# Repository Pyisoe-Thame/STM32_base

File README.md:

# Relay with AC PS and STM32

This is my PCB Design practice project.
Flexible programming expandable with sensors through I2C.

## Screenshots

<p align="center">PCB Design</p>

<p align="center">3D View</p>

## Features

- AC Power Supply to 5V, 3V3
- STM32F103C8T6
- SWD J Tag Connector
- USB Type C 2.0
- USART, I2C
- 5V Relay

## License

[MIT](https://choosealicense.com/licenses/mit/)

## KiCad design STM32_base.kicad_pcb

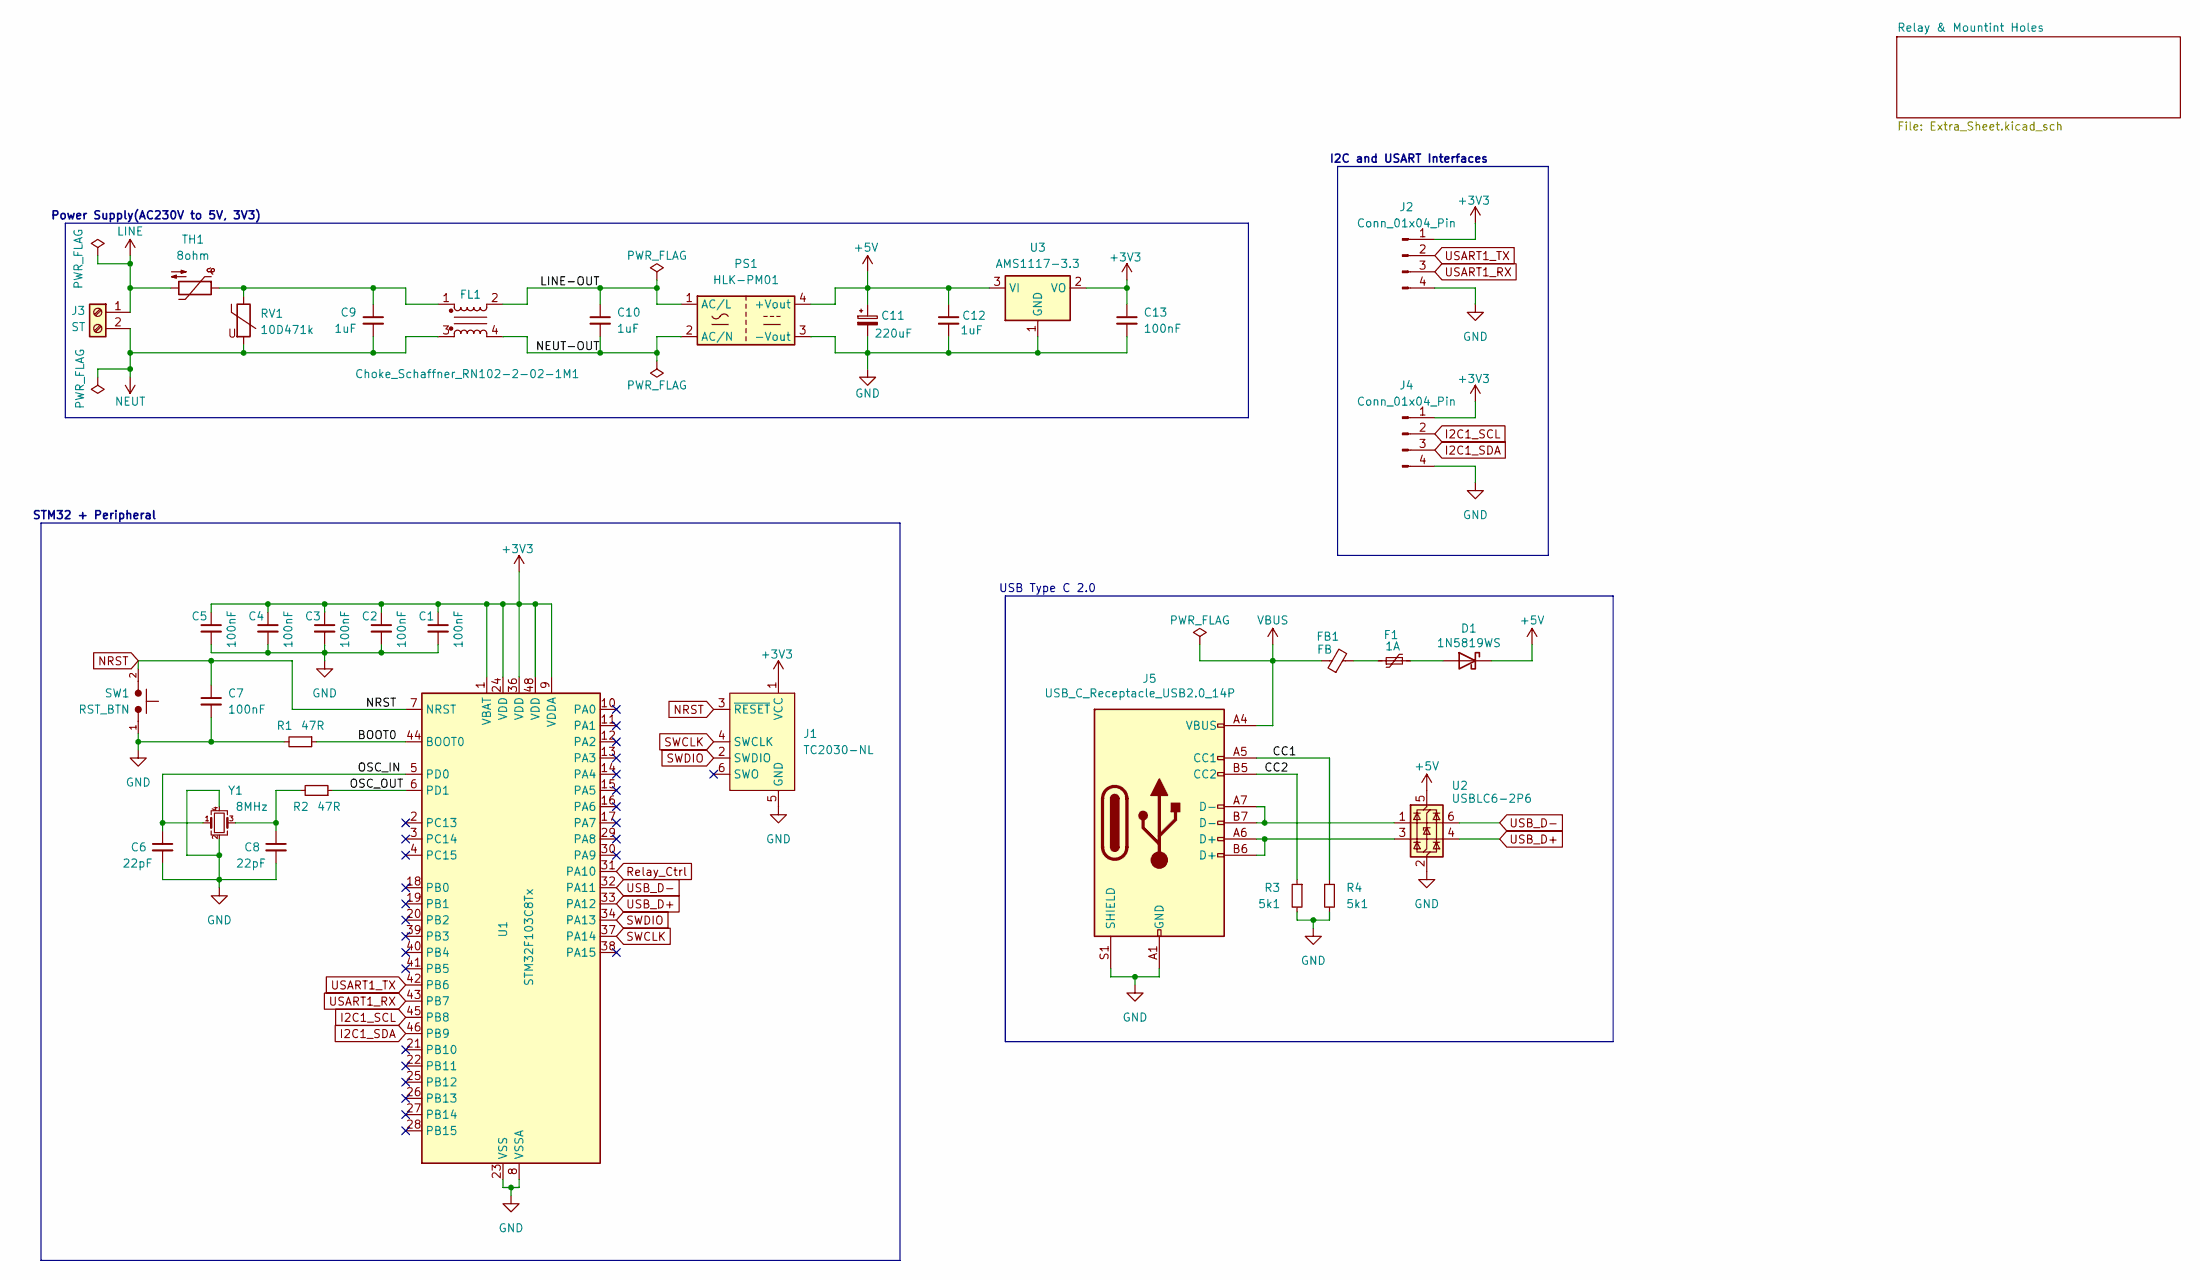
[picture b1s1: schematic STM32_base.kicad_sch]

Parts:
C1, C2, C3, C4, C5, C7, C13: 100nF; C_0402_1005Metric
C6, C8: 22pF; C_0402_1005Metric
C9, C10: 1uF; C_Rect_L18.0mm_W9.0mm_P15.00mm_FKS3_FKP3
C11: 220uF; CP_Elec_10x10
C12: 1uF; C_0603_1608Metric
D1: 1N5819WS; D_SOD-323
F1: 1A; Fuse_1206_3216Metric
FB1: FB; L_0603_1608Metric
FL1: Choke_Schaffner_RN102-2-02-1M1; Choke_Schaffner_RN102-04-14.0x14.0mm
J1: TC2030-NL; Tag-Connect_TC2030-IDC-NL_2x03_P1.27mm_Vertical
J2, J4: Conn_01x04_Pin; PinHeader_1x04_P2.54mm_Vertical
J3: ST; TerminalBlock_Phoenix_MKDS-1,5-2-5.08_1x02_P5.08mm_Horizont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
J5: USB_C_Receptacle_USB2.0_14P; USB_C_Receptacle_HRO_TYPE-C-31-M-12
PS1: HLK-PM01; Converter_ACDC_Hi-Link_HLK-PMxx
R1, R2: 47R; R_0603_1608Metric
R3, R4: 5k1; R_0603_1608Metric
RV1: 10D471k; RV_Disc_D12mm_W4.7mm_P7.5mm
SW1: RST_BTN; SW_PUSH_6mm
TH1: 8ohm; RV_Disc_D12mm_W4.7mm_P7.5mm
U1: STM32F103C8Tx; LQFP-48_7x7mm_P0.5mm
U2: USBLC6-2P6; SOT-666
U3: AMS1117-3.3; SOT-223-3_TabPin2
Y1: 8MHz; Crystal_SMD_3225-4Pin_3.2x2.5mm

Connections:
+3V3: C1.1, C2.1, C3.1, C4.1, C5.1, C13.1, J1.1 (VCC), J2.1, J4.1, U1.1 (VBAT), U1.9 (VDDA), U1.24 (VDD), U1.36 (VDD), U1.48 (VDD), U3.2 (VO)
+5V: C11.1, C12.1, D1.1 (K), PS1.4 (+Vout), U2.5 (VBUS), U3.3 (VI); also elsewhere on the board
/BOOT0: R1.1, U1.44 (BOOT0)
/CC1: J5.A5 (CC1), R4.1
/CC2: J5.B5 (CC2), R3.1
/LINE-OUT: C10.1, FL1.2, PS1.1 (AC/L)
/NEUT-OUT: C10.2, FL1.4, PS1.2 (AC/N)
/OSC_IN: C6.1, U1.5 (PD0), Y1.1
/OSC_OUT: R2.1, U1.6 (PD1)
GND: C1.2, C2.2, C3.2, C4.2, C5.2, C6.2, C7.2, C8.2, C11.2, C12.2, C13.2, J1.5 (GND), J2.4, J4.4, J5.A1 (GND), J5.A12 (GND), J5.B1 (GND), J5.B12 (GND), J5.S1 (SHIELD), PS1.3 (-Vout), R1.2, R3.2, R4.2, SW1.1, U1.8 (VSSA), U1.23 (VSS), U1.35 (VSS), U1.47 (VSS), U2.2 (GND), U3.1 (GND), Y1.2, Y1.4; also elsewhere on the board
I2C1_SCL: J4.2, U1.45 (PB8)
I2C1_SDA: J4.3, U1.46 (PB9)
LINE: J3.1, TH1.2
NEUT: C9.2, FL1.3, J3.2, RV1.2
NRST: C7.1, J1.3 (~RESET), SW1.2, U1.7 (NRST)
unnamed: C8.1, R2.2, Y1.3
unnamed: C9.1, FL1.1, RV1.1, TH1.1
unnamed: D1.2 (A), F1.2
unnamed: F1.1, FB1.2
unnamed: J5.A6 (D+), J5.B6 (D+), U2.3 (I/O2)
unnamed: J5.A7 (D-), J5.B7 (D-), U2.1 (I/O1)
Relay_Ctrl: U1.31 (PA10); also elsewhere on the board
SWCLK: J1.4 (SWCLK), U1.37 (PA14)
SWDIO: J1.2 (SWDIO), U1.34 (PA13)
USART1_RX: J2.3, U1.43 (PB7)
USART1_TX: J2.2, U1.42 (PB6)
USB_D+: U1.33 (PA12), U2.4 (I/O2)
USB_D-: U1.32 (PA11), U2.6 (I/O1)
VBUS: FB1.1, J5.A4 (VBUS), J5.A9 (VBUS), J5.B4 (VBUS), J5.B9 (VBUS)

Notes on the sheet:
I2C and USART Interfaces
STM32 + Peripheral
Power Supply(AC230V to 5V, 3V3)
USB Type C 2.0

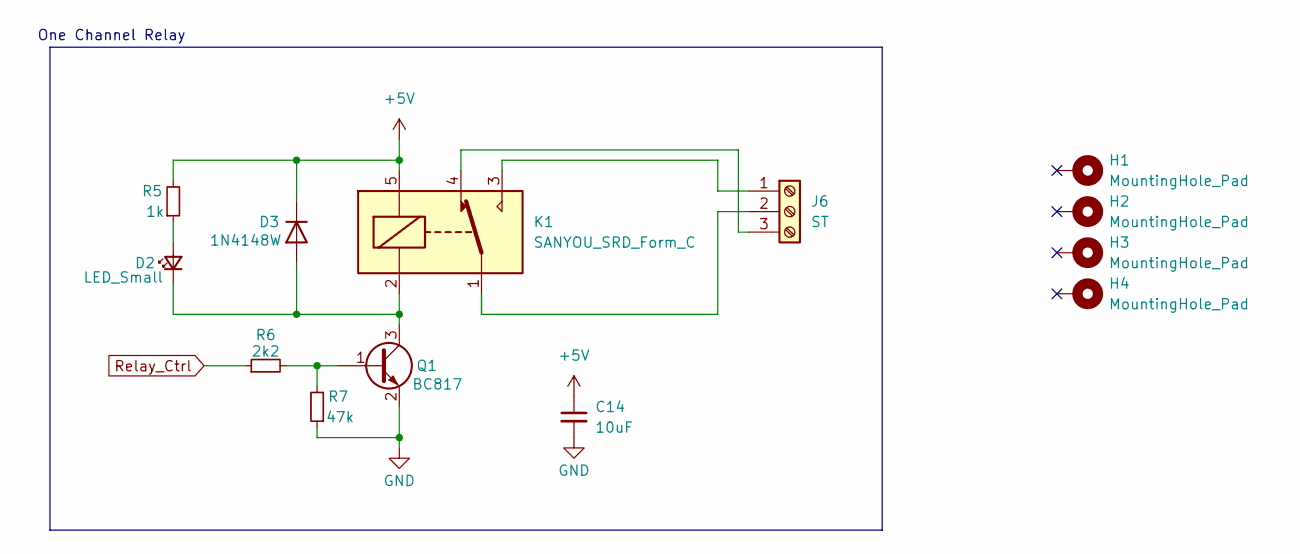
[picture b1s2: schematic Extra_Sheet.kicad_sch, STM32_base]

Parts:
C14: 10uF; C_0805_2012Metric
D2: LED_Small; LED_0603_1608Metric
D3: 1N4148W; D_SOD-123
H1, H2, H3, H4: MountingHole_Pad; MountingHole_3.2mm_M3_Pad_Via
J6: ST; TerminalBlock_Phoenix_MKDS-3-3-5.08_1x03_P5.08mm_Horizontal
K1: SANYOU_SRD_Form_C; Relay_SPDT_SANYOU_SRD_Series_Form_C
Q1: BC817; SOT-23
R5: 1k; R_0603_1608Metric
R6: 2k2; R_0603_1608Metric
R7: 47k; R_0603_1608Metric

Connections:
+5V: C14.1, D3.1 (K), K1.5, R5.2; also elsewhere on the board
GND: C14.2, Q1.2 (E), R7.1; also elsewhere on the board
unnamed: D2.2 (A), R5.1
unnamed: D2.1 (K), D3.2 (A), K1.2, Q1.3 (C)
unnamed: J6.1, K1.3
unnamed: J6.2, K1.1
unnamed: J6.3, K1.4
unnamed: Q1.1 (B), R6.2, R7.2
Relay_Ctrl: R6.1; also elsewhere on the board

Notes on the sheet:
One Channel Relay

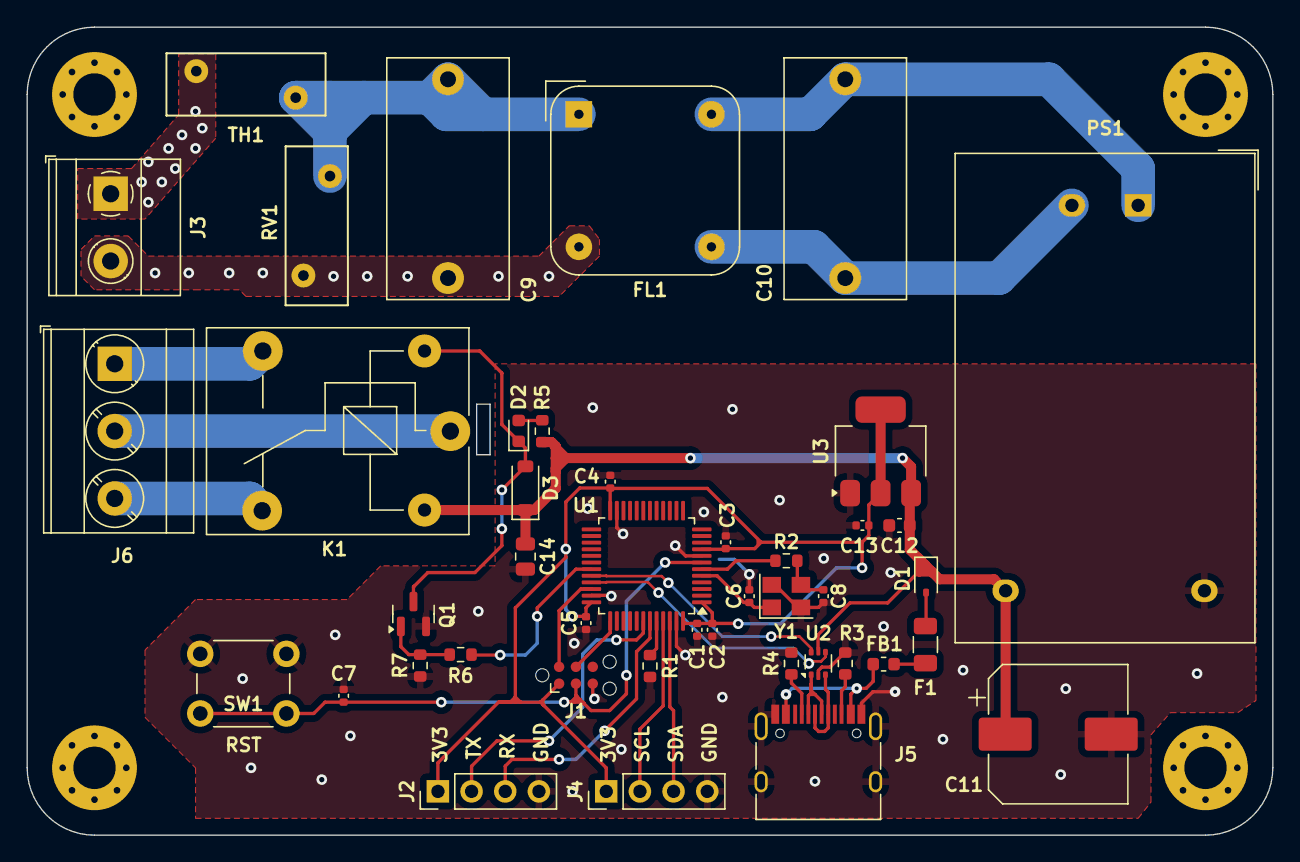
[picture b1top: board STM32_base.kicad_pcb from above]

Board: 2 copper layers, 94.0 x 61.0 mm, 47 parts (0 on the bottom side), 35 nets.

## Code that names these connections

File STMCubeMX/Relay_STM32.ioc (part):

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Mcu.Name=STM32F103C(8-B)Tx
Mcu.Package=LQFP48
Mcu.UserName=STM32F103C8Tx
PA10.Signal=GPIO_Output
PA11.Mode=Device
PA11.Signal=USB_DM
PA12.Mode=Device
PA12.Signal=USB_DP
PA13.Mode=Serial_Wire
PA13.Signal=SYS_JTMS-SWDIO
PA14.Mode=Serial_Wire
PA14.Signal=SYS_JTCK-SWCLK
PB6.Mode=Asynchronous
PB6.Signal=USART1_TX
PB7.Mode=Asynchronous
PB7.Signal=USART1_RX
PB8.Mode=I2C
PB8.Signal=I2C1_SCL
PB9.Mode=I2C
PB9.Signal=I2C1_SDA
PD0-OSC_IN.Mode=HSE-External-Oscillator
PD0-OSC_IN.Signal=RCC_OSC_IN
PD1-OSC_OUT.Mode=HSE-External-Oscillator
PD1-OSC_OUT.Signal=RCC_OSC_OUT
RCC.SYSCLKFreq_VALUE=72000000
RCC.SYSCLKSource=RCC_SYSCLKSOURCE_PLLCLK
board=custom

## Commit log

2024-04-02 schematic
2024-04-03 PCB Components placed
2024-04-08 pcb finished, gerber added
2024-04-08 MX file added, readme added
2024-04-08 schematic pdf added
2024-04-08 3d view and pcb design image added
2024-04-08 image links added to readme file
2024-04-08 label added under images in readme.md
